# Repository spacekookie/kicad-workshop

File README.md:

# Adaconf KiCAD & OpenHardware workshop

This repository documents the KiCAD & OpenHardware workshop given at AdaConf_1. It contains two example projects, documentation as well as the introduction slides shown at the workshop. Further down this README there are alternative project ideas, if you don't like the example projects.

**Follow the slides along [here](slides/introduction/kicad_intro.pdf)**

## Installing KiCAD

KiCAD is free & open source software and can be downloaded from [kicad-pcb.org](http://kicad-pcb.org/download/). It is available on Linux, MacOS and Windows as pre-built binaries. On Linux there are packages for multiple distributions.

The workshop assumes usage of `Kicad 4.0.7`.

If you encounter any issues during installation, check the official [troubleshooting guide](http://kicad-pcb.org/help/known-system-related-issues/) for help.

## Examples

There are two examples in this repository: **symwaf** `simple` and `complete`. Note that you should not attempt to manufacture the simple version! It's missing a few core components that make it programmable. It's only meant as an example. The `complete` variant can also be programmed.

**Simple Project**

- [Schematic](examples/symwaf_simple/schematic.pdf)
- [Board layout](examples/symwaf_simple/circuitboard.pdf)

**Complete Project**

- [Schematic](examples/symwaf_complete/schematic.pdf)
- [Board layout](examples/symwaf_complete/circuitboard.pdf)

For this example there are some step-by-step instructions.

- Creating a [schematic symbol](slides/symbol/kicad_symbol.pdf)
- Creating a [footprint](slides/footprint/kicad_footprint.pdf)

## Alternative Project ideas

Don't like the provided example? Would rather make something from scratch? Here's a few project ideas, including some basic planning docs and datasheets.

- [Shifty](examples/shifty), a shift-register and timer based blinking toy
- [Basic Amplifier](examples/audio), a simple audio amplifier for headphones

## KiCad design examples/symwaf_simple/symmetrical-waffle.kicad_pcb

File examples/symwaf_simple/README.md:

# Symmetrical Waffle

(Name picked by Github random name generator 😉)

This is the simple version of the example project. DO NOT PRODUCE THIS! YOU WILL NOT BE ABLE TO PROGRAM OR RUN IT! Nontheless there are a few things you can learn from this 😄

- Creating a project from scratch
- Creating a schematic symbol & footprint
- Working with KiCAD 3D files (and downloading new ones)
- Going through the workflow to produce a board

## Components

 - AtMega 328
 - 12 ws2812b (Neopixel) LED's

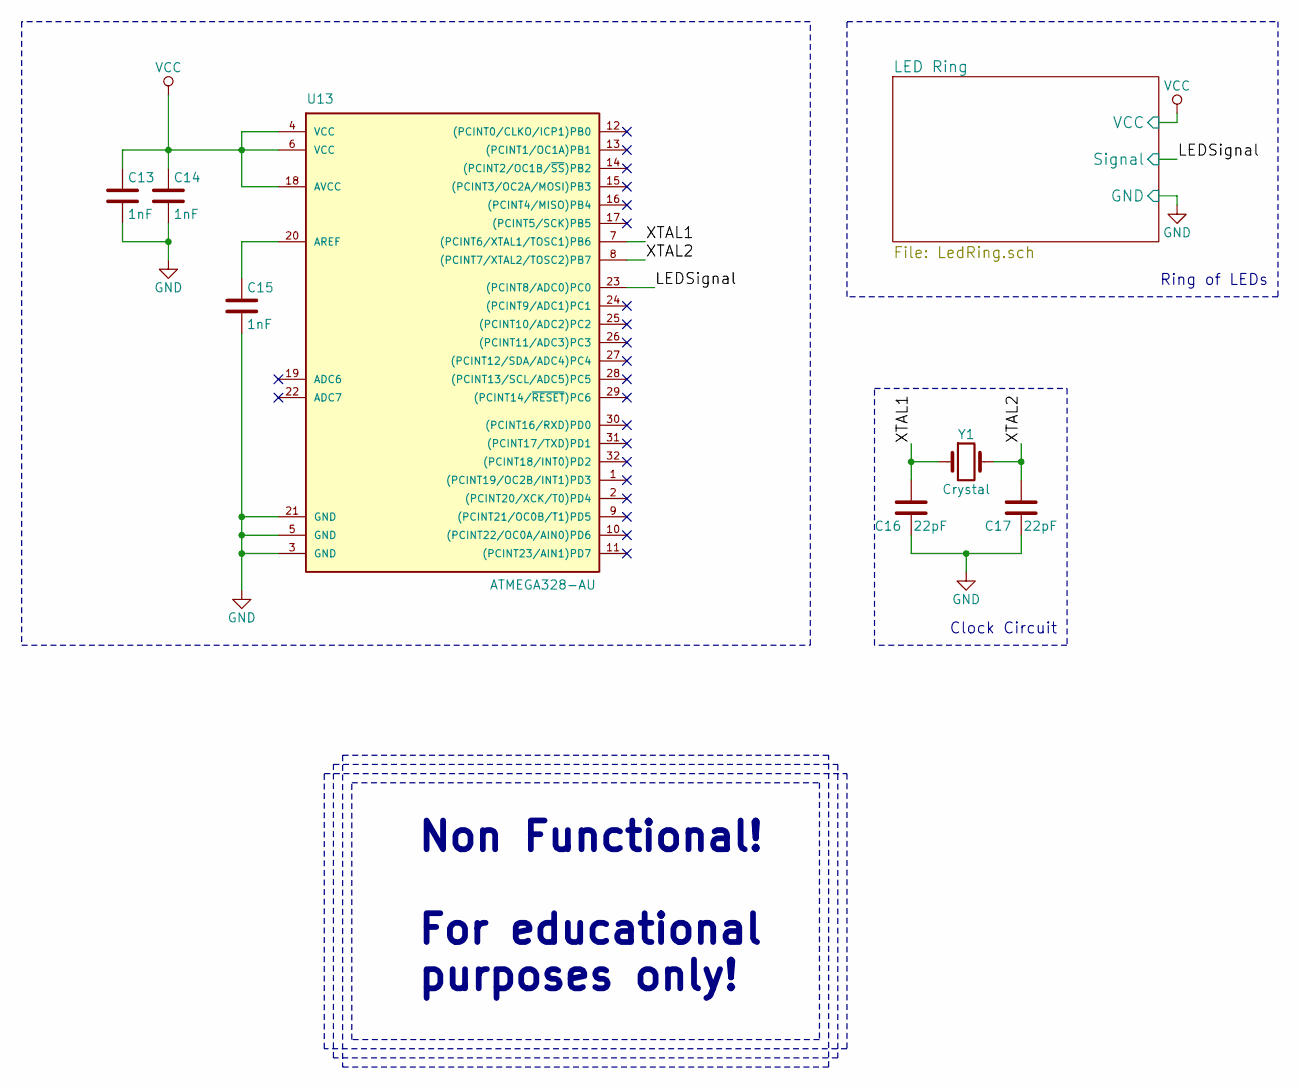
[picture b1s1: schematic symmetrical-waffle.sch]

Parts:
C13, C14, C15: 1nF; C_1206
C16, C17: 22pF; C_1206
U13: ATMEGA328-AU; TQFP-32_7x7mm_Pitch0.8mm
Y1: Crystal; Crystal_SMD_2012-2pin_2.0x1.2mm_HandSoldering

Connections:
/LEDSignal: U13.23 ((PCINT8/ADC0)PC0); also elsewhere on the board
/XTAL1: C16.2, U13.7 ((PCINT6/XTAL1/TOSC1)PB6), Y1.1
/XTAL2: C17.2, U13.8 ((PCINT7/XTAL2/TOSC2)PB7), Y1.2
GND: C13.2, C14.2, C15.2, C16.1, C17.1, U13.3 (GND), U13.5 (GND), U13.21 (GND); also elsewhere on the board
unnamed: C15.1, U13.20 (AREF)
VCC: C13.1, C14.1, U13.4 (VCC), U13.6 (VCC), U13.18 (AVCC); also elsewhere on the board

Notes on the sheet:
Ring of LEDs
Clock Circuit
Non Functional! For educational purposes only!

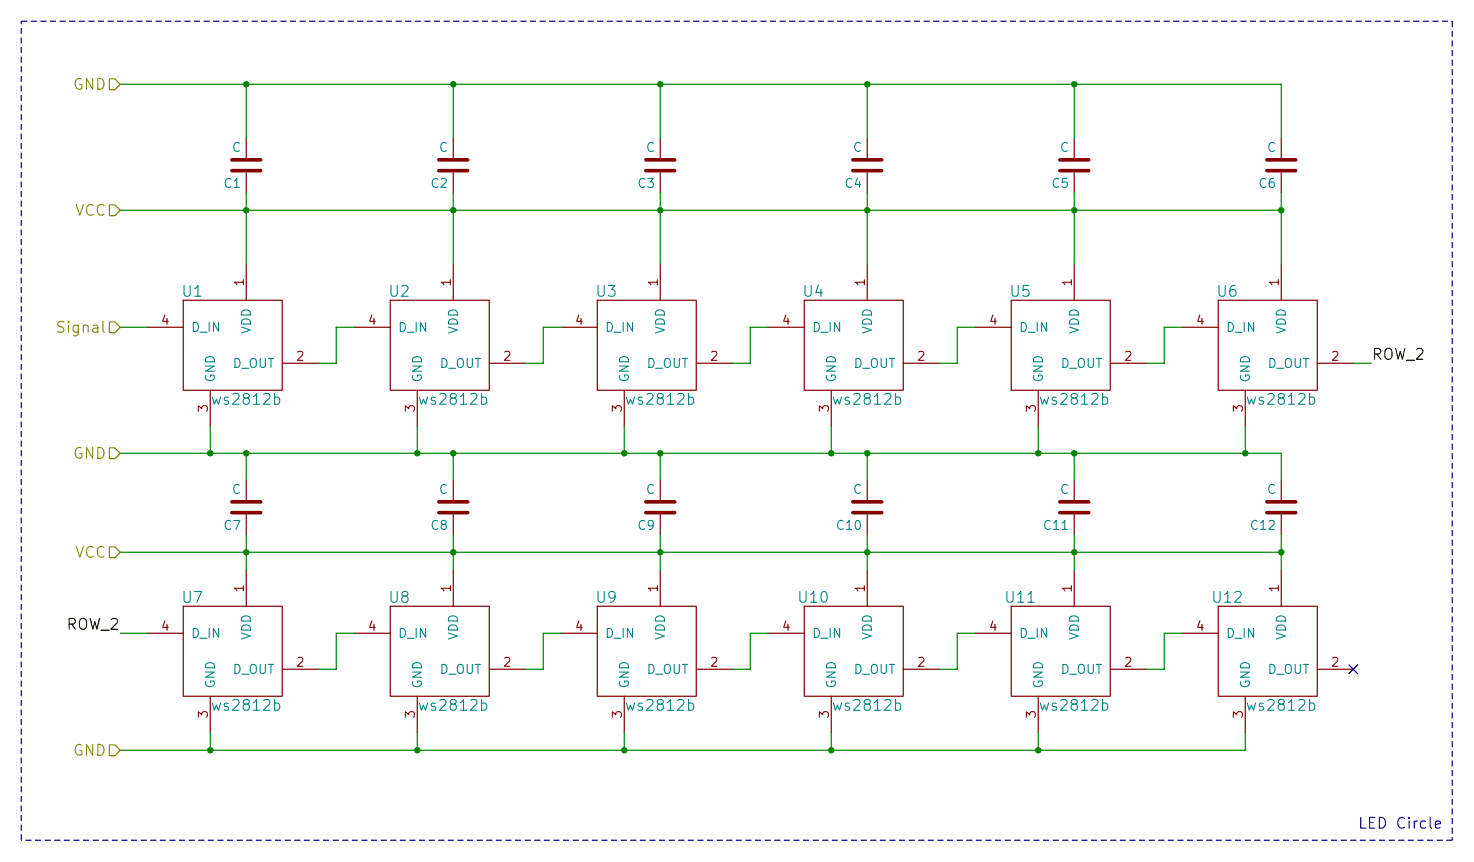
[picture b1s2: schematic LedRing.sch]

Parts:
C1, C2, C3, C4, C5, C6, C7, C8, C9, C10, C11, C12: C; C_1206
U1, U2, U3, U4, U5, U6, U7, U8, U9, U10, U11, U12: ws2812b

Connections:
/LED Ring/ROW_2: U6.2 (D_OUT), U7.4 (D_IN)
/LEDSignal: U1.4 (D_IN); also elsewhere on the board
GND: C1.2, C2.2, C3.2, C4.2, C5.2, C6.2, C7.2, C8.2, C9.2, C10.2, C11.2, C12.2, U1.3 (GND), U2.3 (GND), U3.3 (GND), U4.3 (GND), U5.3 (GND), U6.3 (GND), U7.3 (GND), U8.3 (GND), U9.3 (GND), U10.3 (GND), U11.3 (GND), U12.3 (GND); also elsewhere on the board
unnamed: U1.2 (D_OUT), U2.4 (D_IN)
unnamed: U2.2 (D_OUT), U3.4 (D_IN)
unnamed: U3.2 (D_OUT), U4.4 (D_IN)
unnamed: U4.2 (D_OUT), U5.4 (D_IN)
unnamed: U5.2 (D_OUT), U6.4 (D_IN)
unnamed: U7.2 (D_OUT), U8.4 (D_IN)
unnamed: U8.2 (D_OUT), U9.4 (D_IN)
unnamed: U10.2 (D_OUT), U11.4 (D_IN)
unnamed: U9.2 (D_OUT), U10.4 (D_IN)
unnamed: U11.2 (D_OUT), U12.4 (D_IN)
VCC: C1.1, C2.1, C3.1, C4.1, C5.1, C6.1, C7.1, C8.1, C9.1, C10.1, C11.1, C12.1, U1.1 (VDD), U2.1 (VDD), U3.1 (VDD), U4.1 (VDD), U5.1 (VDD), U6.1 (VDD), U7.1 (VDD), U8.1 (VDD), U9.1 (VDD), U10.1 (VDD), U11.1 (VDD), U12.1 (VDD); also elsewhere on the board

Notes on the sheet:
LED Circle

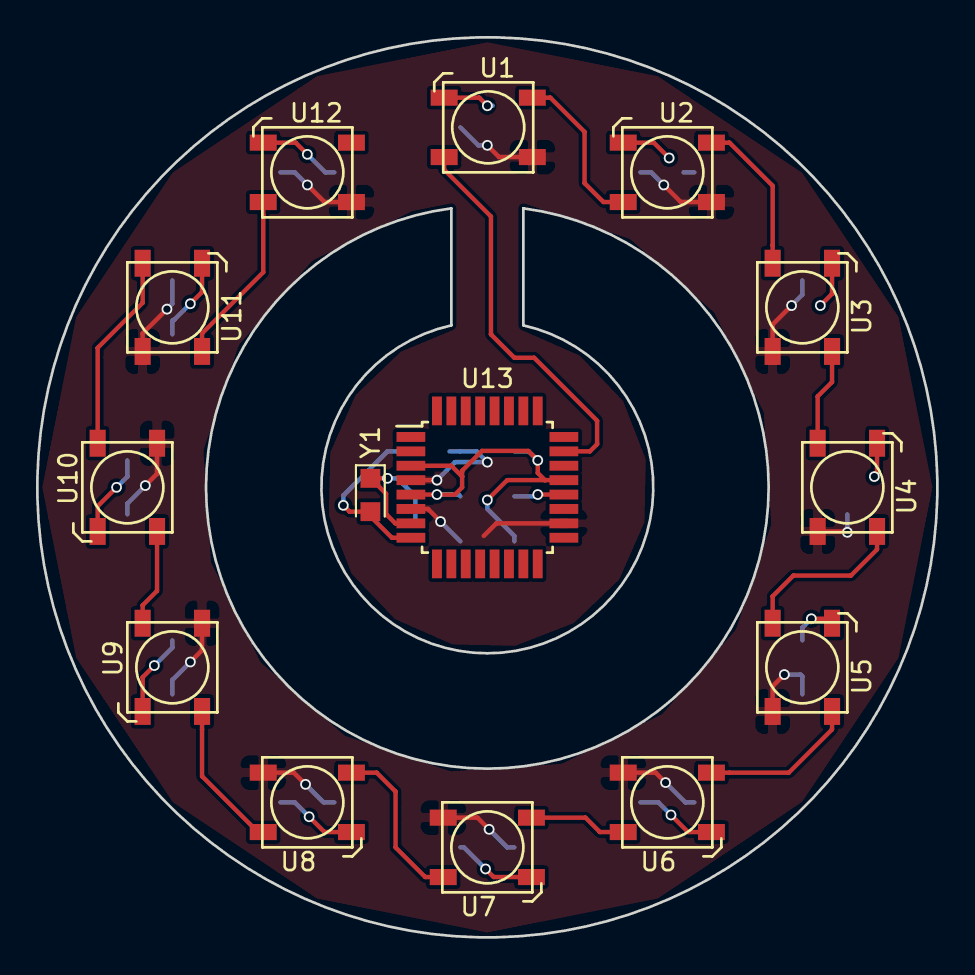
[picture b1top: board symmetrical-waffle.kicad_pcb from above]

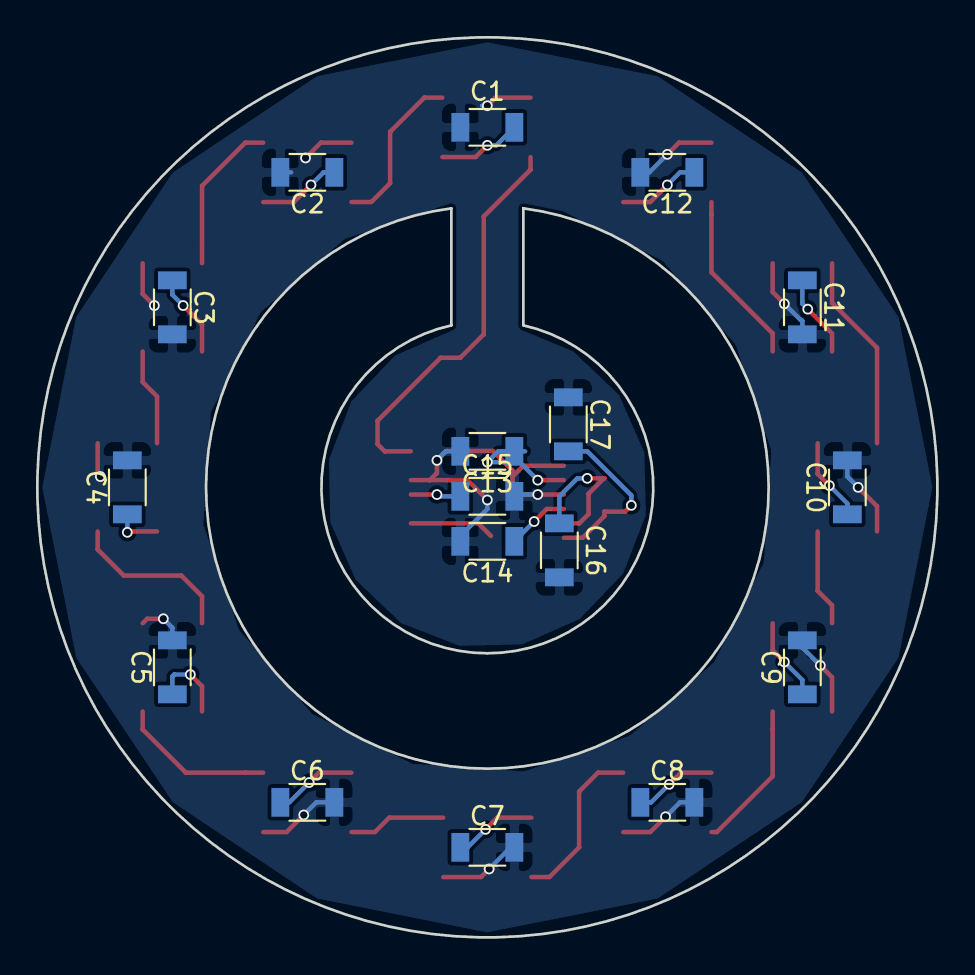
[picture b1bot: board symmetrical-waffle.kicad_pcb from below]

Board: 2 copper layers, 50.0 x 50.0 mm, 31 parts (17 on the bottom side), 17 nets.

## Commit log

2018-03-07 Adding an outline and TODO to the README
2018-03-07 Adding a slides template
2018-03-07 Making them all checkboxes
2018-03-07 Fixing gitignore
2018-03-07 Fixing it again for good measure :D
2018-03-10 Adding an empty kicad example
2018-03-10 Adding the LED ring to the schematic
2018-03-10 Starting to add the arduino
2018-03-10 Finishing the basic schematic
2018-03-10 Adding a power switch and GPIO header
2018-03-10 Updating the example project README
2018-03-10 Adding a small example about footprint scales
2018-03-10 Reannotating
2018-03-11 Working on the more advanced example
2018-03-12 Deleting existing example
2018-03-12 Creating two seperate examples
2018-03-13 Refactoring the two examples
2018-03-13 Working on the "complete" board layout"
2018-03-13 We might want to switch out the switches to something more smaller
2018-03-14 Creating a simpler version of the example board
2018-03-14 Changing the outline of the slides
2018-03-15 Slight slides update
2018-03-15 Adding some pictures to the slides
2018-03-15 Adding more pictures into the slides
2018-03-15 Updating project
2018-03-15 Adding datasheet and preliminary slides
2018-03-15 Updating the README and adding plotted schematics
2018-03-15 Adding link to slides
2018-03-15 Adding some new slides and pdf renders of the complete project
2018-03-15 Updating schematic symbol slides
2018-03-15 Updating links to symbol slides
2018-03-16 Adding footprint tutorial slides
2018-03-16 Adding reference to repository into slides. Updating slides
2018-03-16 Fixing some typos, changing some phrasings in README
2018-03-17 Watching the keynote right now. Adding some more example resources. Fixing a few last issues
2018-03-17 Watching the opening keynote right now ;) Also adding some stuff
